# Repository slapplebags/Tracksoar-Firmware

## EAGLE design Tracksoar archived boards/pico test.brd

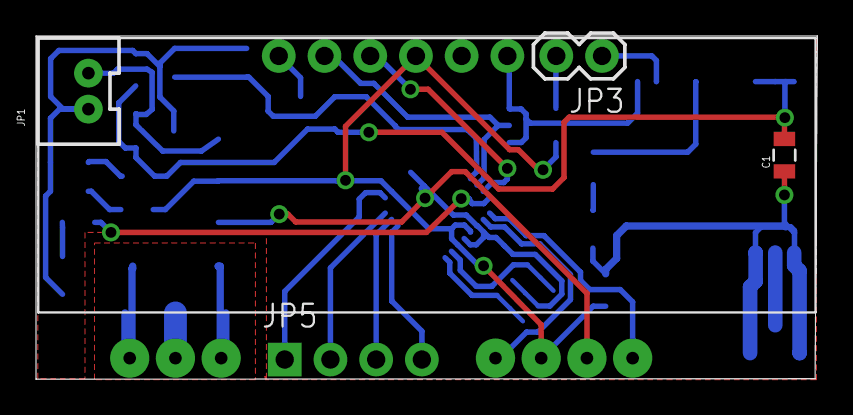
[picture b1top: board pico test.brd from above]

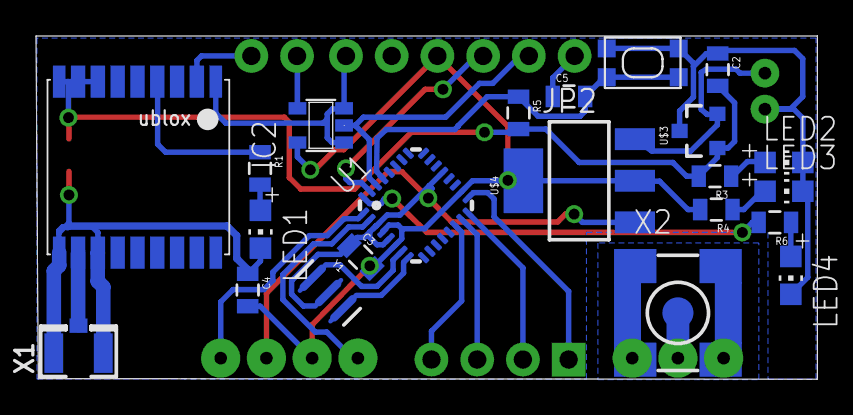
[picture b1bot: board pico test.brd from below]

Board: 2 copper layers, 43.4 x 19.1 mm, 29 parts (23 on the bottom side), 26 nets.

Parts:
C1, C2, C3, C4, C5: 0805
FRAME1: FRAME-LETTER; CREATIVE_COMMONS
IC2: 74AHC1G125DBV; SOT23-5
JP1: M02JST-PTH-VERT; JST-2-PTH-VERT
JP2: 1X06_NO_SILK
JP3: M02PTH; 1X02
JP5: 1X04_NO_SILK
LED1, LED2, LED3, LED4: CHIP-LED0805
R1, R3, R4, R5, R6: 0805
SW1: SPST_TACT-KMR2; KMR2
U1: ATMEGA168MLF; MLF32
U$1: UBLOX_MAX
U$2: RADIOMETRIX-HX1
U$3: LM3480IM4; SOT23-3
U$4: V_REG_MIC2920; SOT223
X1: U.FL
X2: SMA-SMD
Y1: 16MHZ; RESONATOR-SMD

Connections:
3V: C1.2, C2.2, R3.2, R5.2, U$1.7_VCC_IO, U$1.8_VCC, U$1.9_V_RESET, U$3.1
15V: JP1.2, U$3.2, U$4.3
D3: U1.1, U$2.TXD
D4: U1.2, U$2.EN
DTR: C5.1, JP2.1
GND: C1.1, C2.1, C3.1, C4.1, IC2.1, IC2.3, JP1.1, JP2.6, LED1.C, LED2.C, LED3.C, LED4.C, SW1.2, SW1.4, U1.3, U1.5, U1.21, U$1.1_GND, U$1.10_GND, U$1.12_GND, U$2.0V, U$2.RFGND, U$2.RFGND2, U$3.3, U$4.1, X1.1, X1.2, X2.2@1, X2.2@2, X2.2@3, X2.2@4, X2.2@5, X2.2@6, Y1.2
LED: R6.2, U1.32
MISO: JP5.2, U1.16
MOSI: JP5.3, U1.15
unnamed: U$2.RFOUT, X2.1
unnamed: R1.1, U$1.4_TIMEPULSE
unnamed: LED1.A, R1.2
unnamed: U$1.11_RF_IN, X1.3
unnamed: LED2.A, R3.1
unnamed: LED3.A, R4.1
unnamed: C5.2, R5.1, SW1.1, SW1.3, U1.29
unnamed: U1.8, Y1.3
unnamed: U1.7, Y1.1
unnamed: LED4.A, R6.1
RXO: IC2.2, JP2.2, U1.30
SCK: JP5.1, U1.17
SS: JP5.4, U1.14
TX: JP3.1, U$1.2_TXD1
TX-3V3: IC2.4, JP3.2
TXO: JP2.3, U1.31
VCC: C3.2, C4.2, IC2.5, JP2.4, R4.2, U1.4, U1.6, U1.18, U$2.VCC, U$4.2

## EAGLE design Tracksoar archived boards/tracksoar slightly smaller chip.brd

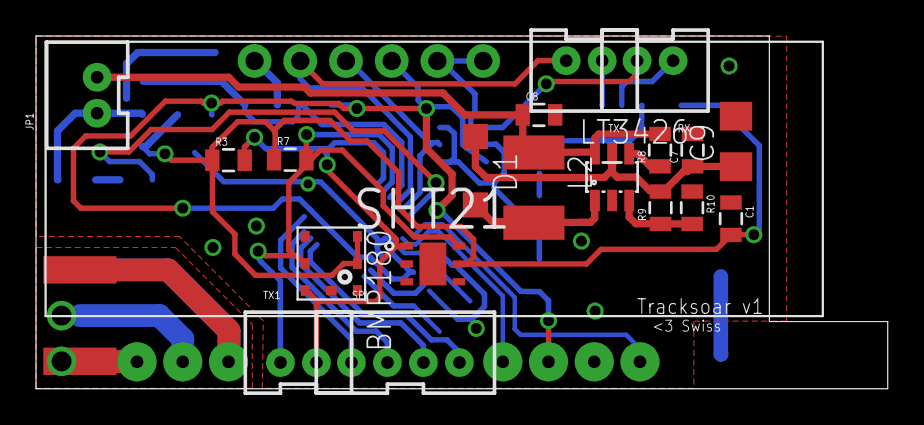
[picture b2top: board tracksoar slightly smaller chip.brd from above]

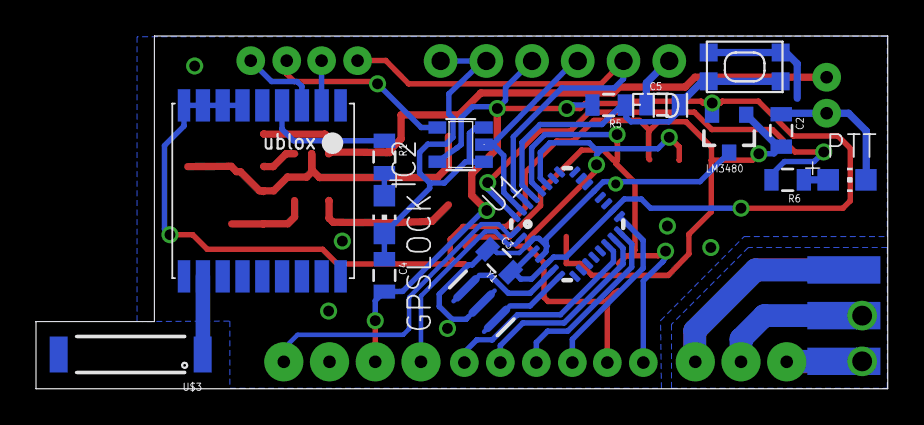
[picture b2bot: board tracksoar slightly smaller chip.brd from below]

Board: 2 copper layers, 47.3 x 19.6 mm, 39 parts (18 on the bottom side), 30 nets.

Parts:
BMP180: BMP180
C1, C2, C3, C4, C5: .1uf; 0805
C7: 22uf; 0805
C8: 10uf; 0805
C9: 100uf; C1206
D1: MBR120VLSFT1; SOD123
FRAME1: FRAME-LETTER; CREATIVE_COMMONS
FTDI: 1X06_NO_SILK
GPSLOCK: CHIP-LED0805
IC2: 74AHC1G125DBV; SOT23-5
J$1: SMA_EDGE; SMA-EDGE
JP1: M02JST-PTH-VERT; JST-2-PTH-VERT
L2: 2.2uh; L1812
LM3480: LM3480IM4; SOT23-3
LT3426: LT3426; SOT23-6
PTT: CHIP-LED0805
R1: 100ohm; 0805
R3, R7: 4.7k; 0805
R5: 10k; 0805
R6: 330ohm; 0805
R8: 1m; 0805
R9: 95.3k; 0805
R10: 30.9k; 0805
RX: RX; JST-2-PTH-VERT
SHT21: SHT21; DFN300X300X110-7N
SPI: JST-4-PTH-VERT
SW1: SPST_TACT-KMR2; KMR2
TX, TX1: TX; JST-2-PTH-VERT
U1: ATMEGA168MLF; MLF32
U$1: UBLOX_MAX
U$2: RADIOMETRIX-HX1
U$3: ANTENNA2SMD3; ANTENNA-CHIP4
Y1: 16MHZ; RESONATOR-SMD

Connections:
3V: BMP180.2, BMP180.3, C1.2, C2.2, LM3480.1, R3.1, R7.1, SHT21.5, U$1.6_V_BCKP, U$1.7_VCC_IO, U$1.8_VCC, U$1.9_V_RESET
15V: C8.1, JP1.2, L2.1, LT3426.6, R8.2
D3: U1.1, U$2.TXD
D4: U1.2, U$2.EN
DTR: C5.1, FTDI.1
GND: BMP180.7, C1.1, C2.1, C3.1, C4.1, C7.2, C8.2, C9.2, FTDI.5, FTDI.6, GPSLOCK.C, IC2.1, IC2.3, J$1.GND@0, J$1.GND@1, J$1.GND@2, J$1.GND@3, JP1.1, LM3480.3, LT3426.2, PTT.C, R10.1, SHT21.2, SW1.2, SW1.4, U1.3, U1.5, U1.21, U$1.1_GND, U$1.10_GND, U$1.12_GND, U$2.0V, U$2.RFGND, U$2.RFGND2, Y1.2
LED: R6.2, U1.32
MISO: SPI.2, U1.16
MOSI: SPI.3, U1.15
unnamed: J$1.SIG, U$2.RFOUT
unnamed: GPSLOCK.A, R1.2
unnamed: U$1.11_RF_IN, U$3.SIG
unnamed: D1.A, L2.2, LT3426.1
unnamed: LT3426.4, R8.1
unnamed: LT3426.3, R9.1, R10.2
unnamed: U1.8, Y1.3
unnamed: C5.2, R5.1, SW1.1, SW1.3, U1.29
unnamed: U1.7, Y1.1
unnamed: PTT.A, R6.1
PPS: R1.1, U$1.4_TIMEPULSE
RX1: RX.1, U$1.3_RXD1
RXO: FTDI.2, TX.2, U1.30
SCK: SPI.1, U1.17
SCL: BMP180.5, R7.2, SHT21.6, TX1.1, U1.28
SDA: BMP180.6, R3.2, SHT21.1, TX1.2, U1.27
SS: SPI.4, U1.14
TX: TX.1, U$1.2_TXD1
TX1: IC2.4, RX.2
TXO: FTDI.3, IC2.2, U1.31
VCC: C3.2, C4.2, C7.1, C9.1, D1.C, FTDI.4, IC2.5, LM3480.2, LT3426.5, R5.2, R9.2, U1.4, U1.6, U1.18, U$2.VCC

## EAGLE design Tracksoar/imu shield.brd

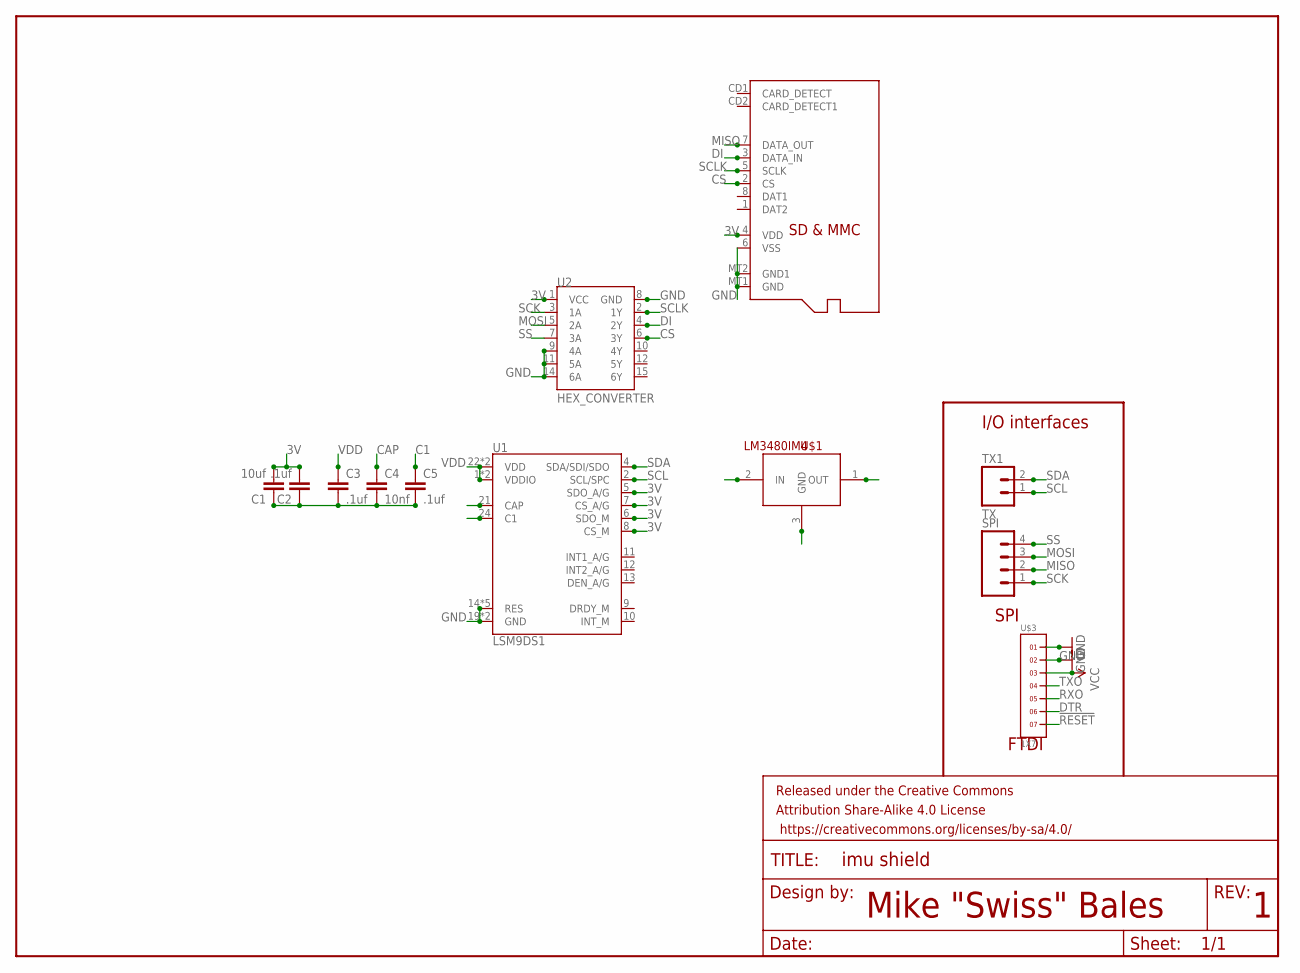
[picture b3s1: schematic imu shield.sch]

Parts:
C1: 10uf; 0805
C2, C3, C5: .1uf; 0805
C4: 10nf; 0805
FRAME1: FRAME-LETTER; CREATIVE_COMMONS
SPI: M04JST-PTH-VERT; JST-4-PTH-VERT
TX1: TX; JST-2-PTH-VERT
U1: LSM9DS1; LGA24-8X4
U2: HEX_CONVERTER; SO016
U$1: LM3480IM4; SOT23-3
U$2: MICROSD
U$3: 1X7

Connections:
3V: C1.2, C2.2, U1.5 (SDO_A/G), U1.6 (SDO_M), U1.7 (CS_A/G), U1.8 (CS_M), U2.1 (VCC), U$2.4 (VDD)
!RESET: U$3.7
C1: C5.1, U1.24 (C1)
CAP: C4.1, U1.21 (CAP)
CS: U2.6 (3Y), U$2.2 (CS)
DI: U2.4 (2Y), U$2.3 (DATA_IN)
DTR: U$3.6
GND: U1.14 (RES), U1.15 (RES), U1.16 (RES), U1.17 (RES), U1.18 (RES), U1.19 (GND), U1.20 (GND), U2.8 (GND), U2.9 (4A), U2.11 (5A), U2.14 (6A), U$1.3 (GND), U$2.6 (VSS), U$2.MT1 (GND), U$2.MT2 (GND1), U$3.1, U$3.2
MISO: SPI.2, U$2.7 (DATA_OUT)
MOSI: SPI.3, U2.5 (2A)
unnamed: C1.1, C2.1, C3.2, C4.2, C5.2
RXO: U$3.5
SCK: SPI.1, U2.3 (1A)
SCL: TX1.1, U1.2 (SCL/SPC)
SCLK: U2.2 (1Y), U$2.5 (SCLK)
SDA: TX1.2, U1.4 (SDA/SDI/SDO)
SS: SPI.4, U2.7 (3A)
TXO: U$3.4
VCC: U$1.2 (IN), U$3.3
VDD: C3.1, U1.1 (VDDIO), U1.3 (VDDIO), U1.22 (VDD), U1.23 (VDD), U$1.1 (OUT)

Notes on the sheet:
Mike "Swiss" Bales
I/O interfaces
SPI
FTDI

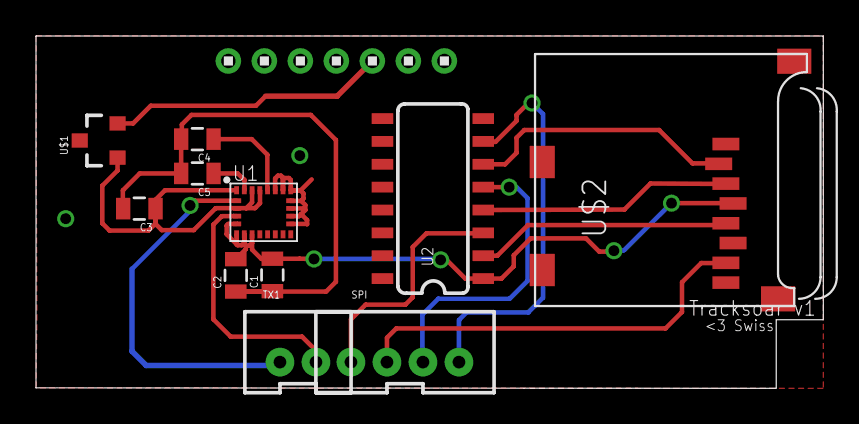
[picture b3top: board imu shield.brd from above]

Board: 2 copper layers, 43.7 x 19.6 mm, 13 parts (0 on the bottom side), 16 nets.

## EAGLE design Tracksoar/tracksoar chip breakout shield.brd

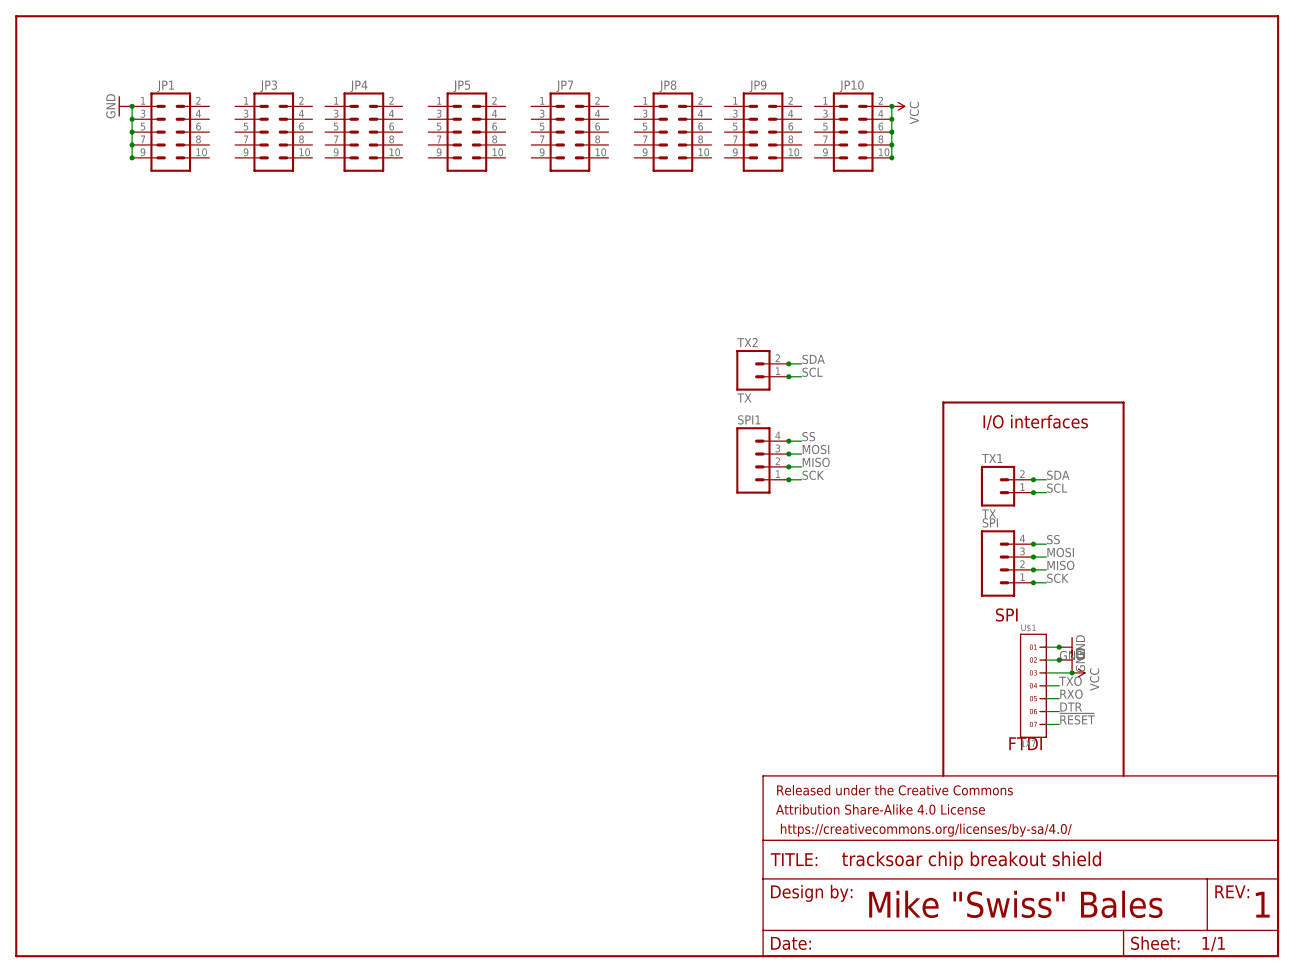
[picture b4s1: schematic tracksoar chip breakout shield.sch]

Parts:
FRAME1: FRAME-LETTER; CREATIVE_COMMONS
JP1, JP3, JP4, JP5, JP7, JP8, JP9, JP10: M05X2NO_SILK; 2X5_NOSILK
SPI, SPI1: M04JST-PTH-VERT; JST-4-PTH-VERT
TX1, TX2: TX; JST-2-PTH-VERT
U$1: 1X7

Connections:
!RESET: U$1.7
DTR: U$1.6
GND: JP1.1, JP1.3, JP1.5, JP1.7, JP1.9, U$1.1, U$1.2
MISO: SPI.2, SPI1.2
MOSI: SPI.3, SPI1.3
RXO: U$1.5
SCK: SPI.1, SPI1.1
SCL: TX1.1, TX2.1
SDA: TX1.2, TX2.2
SS: SPI.4, SPI1.4
TXO: U$1.4
VCC: JP10.2, JP10.4, JP10.6, JP10.8, JP10.10, U$1.3

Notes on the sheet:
Mike "Swiss" Bales
I/O interfaces
SPI
FTDI

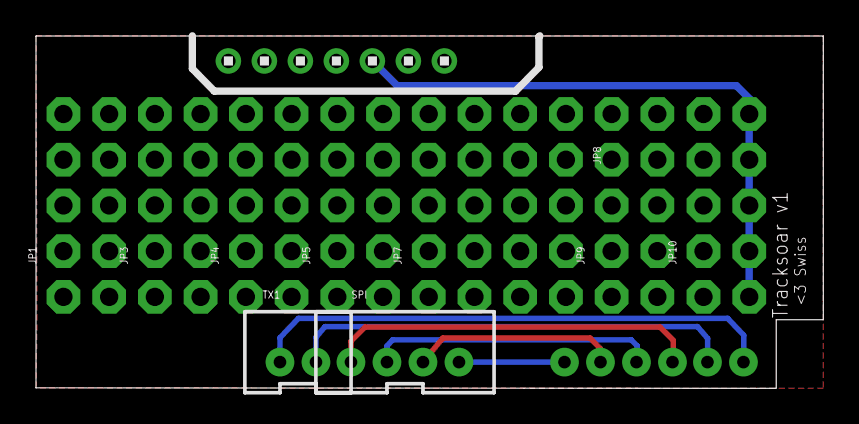
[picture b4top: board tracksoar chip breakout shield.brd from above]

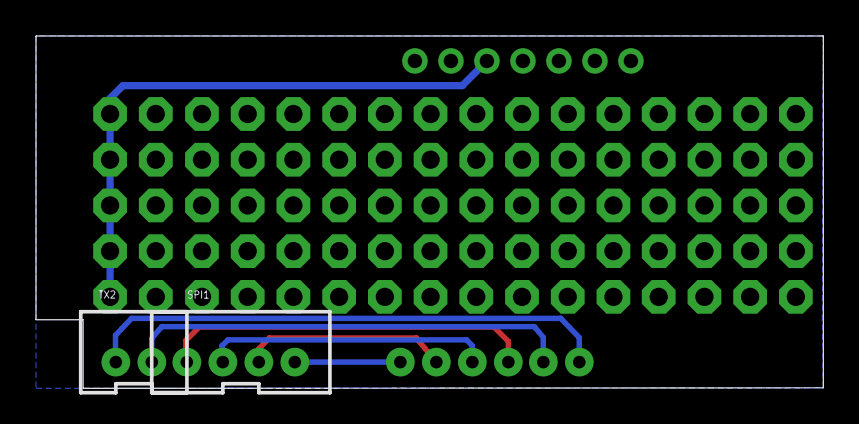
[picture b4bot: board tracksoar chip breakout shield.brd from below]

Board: 2 copper layers, 43.7 x 19.6 mm, 14 parts (2 on the bottom side), 8 nets.

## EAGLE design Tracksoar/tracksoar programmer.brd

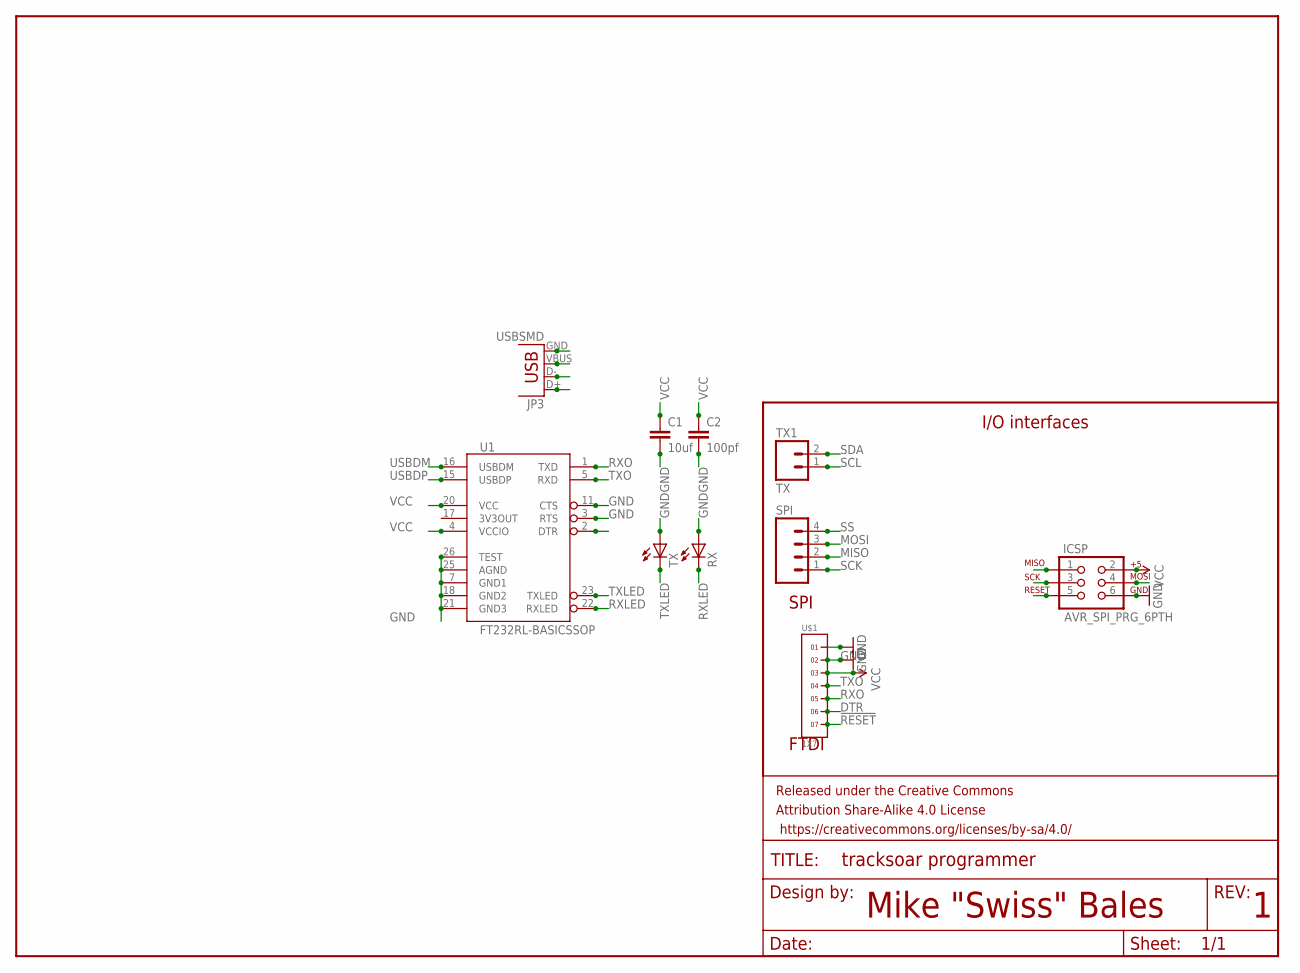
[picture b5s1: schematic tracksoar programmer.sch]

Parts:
C1: 10uf; 0805
C2: 100pf; 0805
FRAME1: FRAME-LETTER; CREATIVE_COMMONS
ICSP: AVR_SPI_PRG_6PTH; 2X3
JP3: USBSMD; USB-MINIB
RX: LEDCHIP-LED0805; CHIP-LED0805
SPI: M04JST-PTH-VERT; JST-4-PTH-VERT
TX: LEDCHIP-LED0805; CHIP-LED0805
TX1: TX; JST-2-PTH-VERT
U1: FT232RL-BASICSSOP; SSOP28DB
U$1: 1X7

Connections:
!RESET: ICSP.5, U$1.7
DTR: U1.2 (DTR), U$1.6
GND: C1.2, C2.2, ICSP.6, JP3.GND, RX.A, TX.A, U1.3 (RTS), U1.7 (GND1), U1.11 (CTS), U1.18 (GND2), U1.21 (GND3), U1.25 (AGND), U1.26 (TEST), U$1.1, U$1.2
MISO: ICSP.1, SPI.2
MOSI: ICSP.4, SPI.3
RXLED: RX.C, U1.22 (RXLED)
RXO: U1.1 (TXD), U$1.5
SCK: ICSP.3, SPI.1
SCL: TX1.1
SDA: TX1.2
SS: SPI.4
TXLED: TX.C, U1.23 (TXLED)
TXO: U1.5 (RXD), U$1.4
USBDM: JP3.D-, U1.16 (USBDM)
USBDP: JP3.D+, U1.15 (USBDP)
VCC: C1.1, C2.1, ICSP.2, JP3.VBUS, U1.4 (VCCIO), U1.20 (VCC), U$1.3

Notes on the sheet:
Mike "Swiss" Bales
I/O interfaces
SPI
FTDI

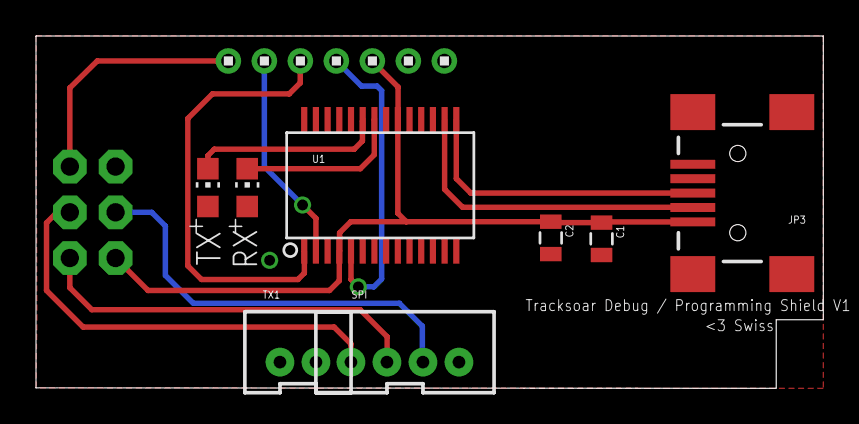
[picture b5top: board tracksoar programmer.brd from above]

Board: 2 copper layers, 43.7 x 19.6 mm, 11 parts (1 on the bottom side), 13 nets.

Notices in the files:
parts and their libraries:
SparkFun-PowerIC: Licensing: Creative Commons ShareAlike 4.0 International - https://creativecommons.org/licenses/by-sa/4.0
SparkFun-Aesthetics: Released under the Creative Commons Attribution Share-Alike 4.0 License
SparkFun-Aesthetics: https://creativecommons.org/licenses/by-sa/4.0
